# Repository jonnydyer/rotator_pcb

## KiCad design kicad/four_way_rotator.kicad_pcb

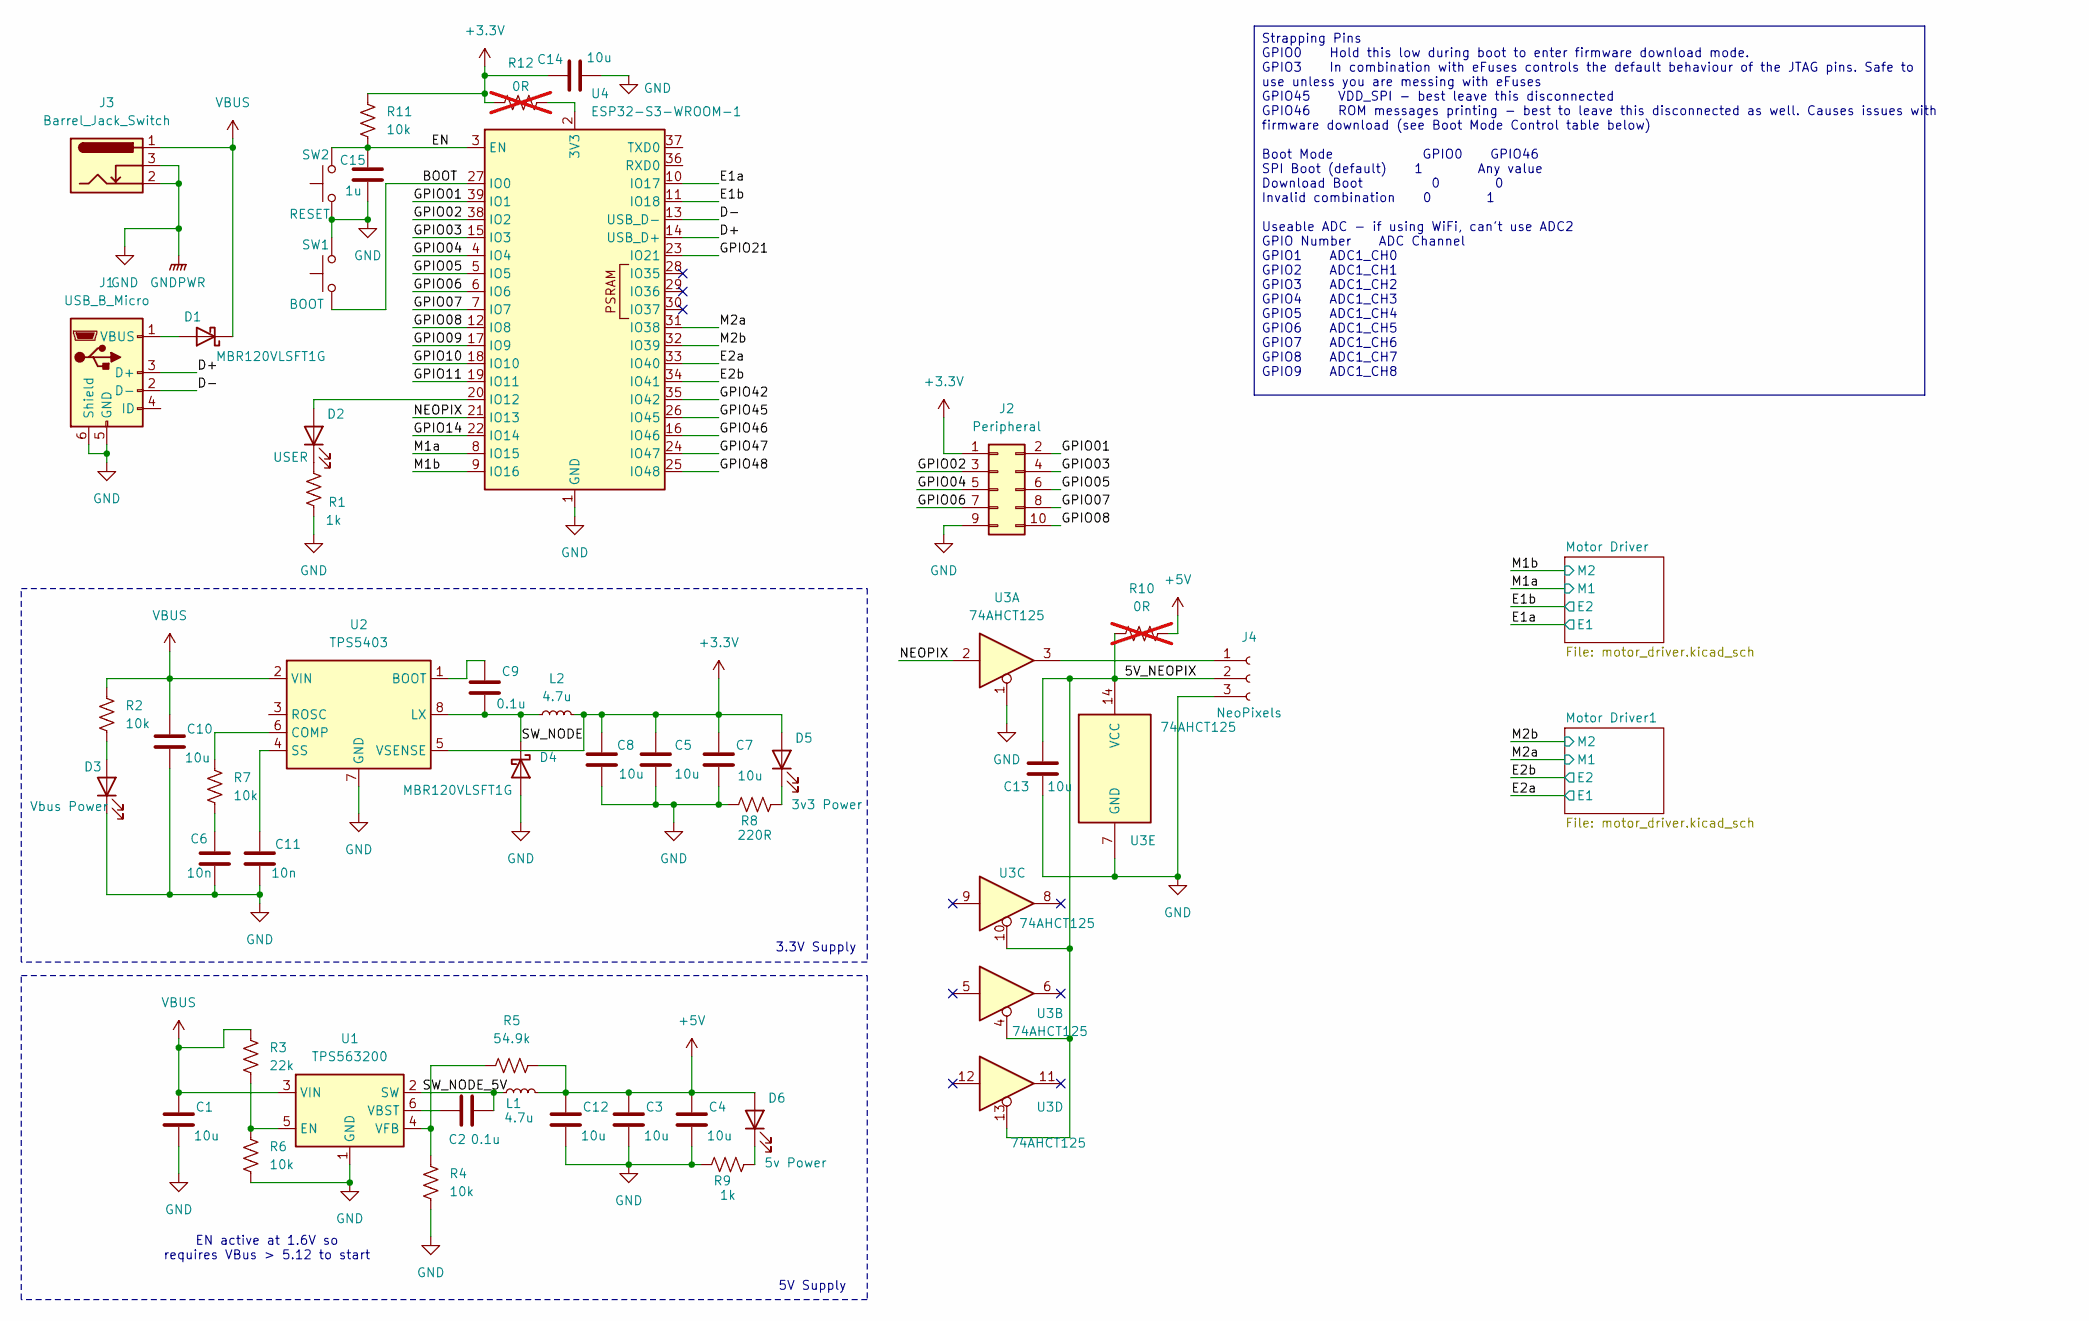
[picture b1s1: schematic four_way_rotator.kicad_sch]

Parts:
C1, C3, C4, C5, C7, C8, C10, C12, C13, C14: 10u; C_1206_3216Metric_Pad1.33x1.80mm_HandSolder; Mouser PN 187-CL31A106MBHNNNE
C2, C9: 0.1u; C_0603_1608Metric_Pad1.08x0.95mm_HandSolder; Mfr PN CL10A104KA8NNNC
C6: 10n; C_0603_1608Metric_Pad1.08x0.95mm_HandSolder; Mfr PN CL10B103KC8NNNC; Mouser PN 187-CL10B103KC8NNNC
C11: 10n; C_0603_1608Metric_Pad1.08x0.95mm_HandSolder; Mouser PN 187-CL10B103KC8NNNC
C15: 1u; C_0805_2012Metric_Pad1.18x1.45mm_HandSolder; Mouser PN 187-CL21B105KBFNNNE
D1, D4: MBR120VLSFT1G; D_SOD-123F; Mfr PN MBR120VLSFT1G
D2: USER; LED_0805_2012Metric_Pad1.15x1.40mm_HandSolder; Mfr PN 150080BS75000; Mouser PN 710-150080BS75000
D3: Vbus Power; LED_0805_2012Metric_Pad1.15x1.40mm_HandSolder; Mfr PN 5975906507F
D5: 3v3 Power; LED_0805_2012Metric_Pad1.15x1.40mm_HandSolder; Mfr PN 150080RS75000; Mouser PN 710-150080RS75000
D6: 5v Power; LED_0805_2012Metric_Pad1.15x1.40mm_HandSolder; Mfr PN HSMA-C190
J1: USB_B_Micro; USB_Micro-B_Molex-105017-0001; Mfr PN 105017-0001; Mouser PN 538-105017-0001
J2: Peripheral; PinHeader_2x05_P2.54mm_Vertical_SMD
J3: Barrel_Jack_Switch; BarrelJack_Wuerth_6941xx301002; Mouser PN 710-694106301002
J4: NeoPixels; Molex_Micro-Fit_3.0_43650-0300_1x03_P3.00mm_Horizontal; Mfr PN 43650-0300; Mouser PN 538-43650-0300
L1, L2: 4.7u; L_TDK_SLF6025; Mouser PN 810-CLF6045NIT4R7ND
R1, R9: 1k; R_0603_1608Metric_Pad0.98x0.95mm_HandSolder; Mfr PN CQ03SAF1001T5E; Mouser PN 303-CQ03SAF1001T5E
R2, R4, R6, R7, R11: 10k; R_0603_1608Metric_Pad0.98x0.95mm_HandSolder; Mfr PN CQ03WAF1002T5E; Mouser PN 303-CQ03WAF1002T5E
R3: 22k; R_0603_1608Metric_Pad0.98x0.95mm_HandSolder; Mfr PN 0603WAF2202T5E; Mouser PN 303-0603WAF2202T5E
R5: 54.9k; R_0603_1608Metric_Pad0.98x0.95mm_HandSolder; Mfr PN RT0603FRE0754K9L; Mouser PN 603-RT0603FRE0754K9L
R8: 220R; R_0603_1608Metric_Pad0.98x0.95mm_HandSolder; Mfr PN CQ03WAF2200T5E; Mouser PN 303-CQ03WAF2200T5E
R10, R12: 0R; R_0402_1005Metric_Pad0.72x0.64mm_HandSolder; Mfr PN RMCF0402ZT0R00; not fitted
SW1: BOOT; SW_SPST_Omron_B3FS-101xP; Mfr PN B3FS-1015; Mouser PN 653-B3FS1015
SW2: RESET; SW_SPST_Omron_B3FS-101xP; Mfr PN B3FS-1015; Mouser PN 653-B3FS1015
U1: TPS563200; SOT-23-6; Mouser PN 595-TPS563200DDCT
U2: TPS5403; SOIC-8_3.9x4.9mm_P1.27mm; Mouser PN 595-TPS5403DR
U3: 74AHCT125; SSOP-14_5.3x6.2mm_P0.65mm; Mfr PN SN74AHCT125DBR; Mouser PN 595-SN74AHCT125DBR
U4: ESP32-S3-WROOM-1; Mouser PN 356-ESP32S3WM1UN16R8

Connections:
+3.3V: C5.1, C7.1, C8.1, C14.1, D5.2 (A), J2.1, L2.2, R11.1, R12.2, U2.5 (VSENSE); also elsewhere on the board
+5V: C3.1, C4.1, C12.1, D6.2 (A), L1.2, R5.2, R10.1
/5V_NEOPIX: C13.2, J4.2, R10.2, U3.4, U3.10, U3.13, U3.14 (VCC)
/BOOT: SW1.1, U4.27 (IO0)
/D+: J1.3 (D+), U4.14 (USB_D+)
/D-: J1.2 (D-), U4.13 (USB_D-)
/E1a: U4.10 (IO17); also elsewhere on the board
/E1b: U4.11 (IO18); also elsewhere on the board
/E2a: U4.33 (IO40); also elsewhere on the board
/E2b: U4.34 (IO41); also elsewhere on the board
/EN: C15.1, R11.2, SW2.2, U4.3 (EN)
/GPIO01: J2.2, U4.39 (IO1)
/GPIO02: J2.3, U4.38 (IO2)
/GPIO03: J2.4, U4.15 (IO3)
/GPIO04: J2.5, U4.4 (IO4)
/GPIO05: J2.6, U4.5 (IO5)
/GPIO06: J2.7, U4.6 (IO6)
/GPIO07: J2.8, U4.7 (IO7)
/GPIO08: J2.10, U4.12 (IO8)
/GPIO09: U4.17 (IO9)
/GPIO10: U4.18 (IO10)
/GPIO11: U4.19 (IO11)
/GPIO14: U4.22 (IO14)
/GPIO21: U4.23 (IO21)
/GPIO42: U4.35 (IO42)
/GPIO45: U4.26 (IO45)
/GPIO46: U4.16 (IO46)
/GPIO47: U4.24 (IO47)
/GPIO48: U4.25 (IO48)
/M1a: U4.8 (IO15); also elsewhere on the board
/M1b: U4.9 (IO16); also elsewhere on the board
/M2a: U4.31 (IO38); also elsewhere on the board
/M2b: U4.32 (IO39); also elsewhere on the board
/NEOPIX: U3.2, U4.21 (IO13)
/SW_NODE: C9.2, D4.1 (K), L2.1, U2.8 (LX)
/SW_NODE_5V: C2.2, L1.1, U1.2 (SW)
GND: C1.2, C3.2, C4.2, C5.2, C6.2, C7.2, C8.2, C10.2, C11.2, C12.2, C13.1, C14.2, C15.2, D3.1 (K), D4.2 (A), J1.5 (GND), J1.6 (Shield), J2.9, J3.2, J3.3, J4.3, R1.1, R4.2, R6.2, R8.1, R9.1, SW1.2, SW2.1, U1.1 (GND), U2.7 (GND), U3.1, U3.7 (GND), U4.1 (GND), U4.40 (GND), U4.41 (GND); also elsewhere on the board
unnamed: C6.1, R7.2
unnamed: D1.2 (A), J1.1 (VBUS)
unnamed: D2.2 (A), U4.20 (IO12)
unnamed: D2.1 (K), R1.2
unnamed: D3.2 (A), R2.2
unnamed: D5.1 (K), R8.2
unnamed: D6.1 (K), R9.2
unnamed: J4.1, U3.3
unnamed: R3.2, R6.1, U1.5 (EN)
unnamed: C2.1, U1.6 (VBST)
unnamed: R4.1, R5.1, U1.4 (VFB)
unnamed: C9.1, U2.1 (BOOT)
unnamed: R7.1, U2.6 (COMP)
unnamed: C11.1, U2.4 (SS)
unnamed: R12.1, U4.2 (3V3)
VBUS: C1.1, C10.1, D1.1 (K), J3.1, R2.1, R3.1, U1.3 (VIN), U2.2 (VIN); also elsewhere on the board

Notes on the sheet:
5V Supply
EN active at 1.6V so requires VBus > 5.12 to start
3.3V Supply
Strapping Pins GPIO0 Hold this low during boot to enter firmware download mode. GPIO3 In combination with eFuses controls the default behaviour of the JTAG pins. Safe to use unless you are messing with eFuses GPIO45 VDD_SPI - best leave this disconnected GPIO46 ROM messages printing - best to leave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

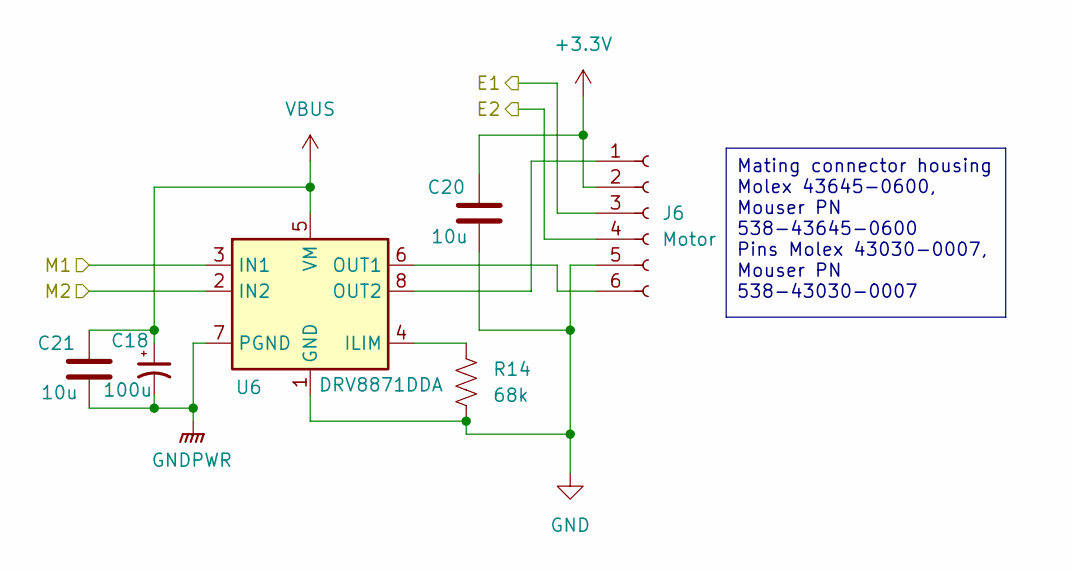
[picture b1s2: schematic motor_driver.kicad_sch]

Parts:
C18: 100u; CP_Elec_6.3x7.7; Mfr PN UWT1V101MCL1GS; Mouser PN 647-UWT1V101MCL1S
C20, C21: 10u; C_1206_3216Metric_Pad1.33x1.80mm_HandSolder; Mouser PN 187-CL31A106MBHNNNE
J6: Motor; Molex_Micro-Fit_3.0_43650-0600_1x06_P3.00mm_Horizontal; Mouser PN 538-43650-0600
R14: 68k; R_0603_1608Metric_Pad0.98x0.95mm_HandSolder; Mfr PN 0603WAF6802T5E; Mouser PN 303-0603WAF6802T5E
U6: DRV8871DDA; Texas_HTSOP-8-1EP_3.9x4.9mm_P1.27mm_EP2.95x4.9mm_Mask2.4x3.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; Mfr PN DRV8871DDAR; Mouser PN 595-DRV8871DDAR

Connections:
+3.3V: C20.2, J6.2; also elsewhere on the board
/E1a: J6.3; also elsewhere on the board
/E1b: J6.4; also elsewhere on the board
/M1a: U6.3 (IN1); also elsewhere on the board
/M1b: U6.2 (IN2); also elsewhere on the board
GND: C18.2, C20.1, C21.1, J6.5, R14.2, U6.1 (GND), U6.7 (GND), U6.9 (GND); also elsewhere on the board
unnamed: J6.1, U6.8 (OUT2)
unnamed: J6.6, U6.6 (OUT1)
unnamed: R14.1, U6.4 (ILIM)
VBUS: C18.1, C21.2, U6.5 (VM); also elsewhere on the board

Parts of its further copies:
C16: 100u; CP_Elec_6.3x7.7; Mfr PN UWT1V101MCL1GS; Mouser PN 647-UWT1V101MCL1S
C17, C19: 10u; C_1206_3216Metric_Pad1.33x1.80mm_HandSolder; Mouser PN 187-CL31A106MBHNNNE
J5: Motor; Molex_Micro-Fit_3.0_43650-0600_1x06_P3.00mm_Horizontal; Mouser PN 538-43650-0600
R13: 68k; R_0603_1608Metric_Pad0.98x0.95mm_HandSolder; Mfr PN 0603WAF6802T5E; Mouser PN 303-0603WAF6802T5E
U5: DRV8871DDA; Texas_HTSOP-8-1EP_3.9x4.9mm_P1.27mm_EP2.95x4.9mm_Mask2.4x3.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; Mfr PN DRV8871DDAR; Mouser PN 595-DRV8871DDAR

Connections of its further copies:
+3.3V: C19.2, J5.2; also elsewhere on the board
/E2a: J5.3; also elsewhere on the board
/E2b: J5.4; also elsewhere on the board
/M2a: U5.3 (IN1); also elsewhere on the board
/M2b: U5.2 (IN2); also elsewhere on the board
GND: C16.2, C17.1, C19.1, J5.5, R13.2, U5.1 (GND), U5.7 (GND), U5.9 (GND); also elsewhere on the board
unnamed: J5.1, U5.8 (OUT2)
unnamed: J5.6, U5.6 (OUT1)
unnamed: R13.1, U5.4 (ILIM)
VBUS: C16.1, C17.2, U5.5 (VM); also elsewhere on the board

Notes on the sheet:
Mating connector housing Molex 43645-0600, Mouser PN 538-43645-0600 Pins Molex 43030-0007, Mouser PN 538-43030-0007

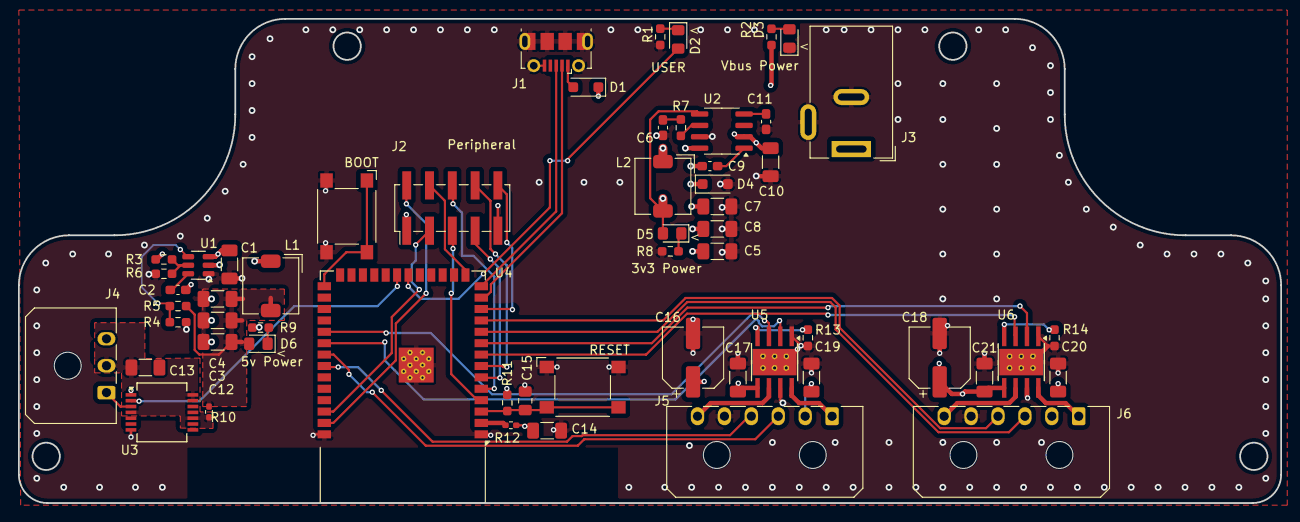
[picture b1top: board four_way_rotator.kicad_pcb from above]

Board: 4 copper layers, 140.7 x 54.0 mm, 57 parts (0 on the bottom side), 49 nets.

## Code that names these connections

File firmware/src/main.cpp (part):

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#include "main.h"

#define USER_LED_PIN 12
#define M1A_PIN 15
#define M1B_PIN 16
#define M2A_PIN 38
#define M2B_PIN 39
#define E1A_PIN 17
#define E1B_PIN 18
#define E2A_PIN 40
#define E2B_PIN 41
#define NEOPIX_PIN 13

// MCPWM configuration
#define MCPWM_FREQ 20000     // PWM frequency in Hz
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
void setup_mcpwm() {
  // Motor 1 MCPWM configuration
  mcpwm_gpio_init(MCPWM_UNIT, MCPWM0A, M1A_PIN);
  mcpwm_gpio_init(MCPWM_UNIT, MCPWM0B, M1B_PIN);
  
  // Motor 2 MCPWM configuration
  mcpwm_gpio_init(MCPWM_UNIT, MCPWM1A, M2A_PIN);
  mcpwm_gpio_init(MCPWM_UNIT, MCPWM1B, M2B_PIN);
  
  // Set MCPWM parameters
  mcpwm_config_t pwm_config;
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
void setup_pins() {
  pinMode(USER_LED_PIN, OUTPUT);       // User LED for debugging
  pinMode(NEOPIX_PIN, OUTPUT);         // NeoPixel LED Data output
  
  // Encoder pins
  pinMode(E1A_PIN, INPUT);             // Encoder 1 A
  pinMode(E1B_PIN, INPUT);             // Encoder 1 B
  pinMode(E2A_PIN, INPUT);             // Encoder 2 A
  pinMode(E2B_PIN, INPUT);             // Encoder 2 B
}

void setup_serial() {
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  ESP32Encoder::useInternalWeakPullResistors = puType::up;
  
  // Encoder 1
  encoder1.attachFullQuad(E1A_PIN, E1B_PIN);
  encoder1.setCount(0);
  
  // Encoder 2
  encoder2.attachFullQuad(E2A_PIN, E2B_PIN);
  encoder2.setCount(0);
  
  g_last_velocity_calc_time = millis();
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
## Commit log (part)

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2025-03-22 initial add
2025-03-29 Fixed feedback node routing
2025-06-15 Lot of changes to get us to a stable MVP.
2025-07-18 Latest working rotator firmware
2025-07-18 fixed rollover issues
2025-09-30 A bunch of updates to allow connection to a wifi network
2025-10-05 a bunch of fixes
2025-10-11 Added not about belt circumference ot README
2025-12-25 complete rework of angle mapping to fix 360 rotation bug
2025-12-25 Added involute gear
